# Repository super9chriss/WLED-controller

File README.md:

# WLED controller
A ESP32 C3 based microcontroller which is made to be used with WLED to use 12V or 24V ledsttrips.
I made this project since i want to add some lighting to my wall since its very dark, i wanted to learn something from this project so i made it into a devboard instead of a simpeler PCB design.
You can attach a 12 or 24V power supply to the Vin port which will directly power the ledstrip so this needs to have the same voltage rating and you can then use the ESP32 to adress the ledstrip.
<div align="center">

</div>

## Features

* **Microcontroller:** ESP32-C3-WROOM-02 with Wi-Fi and Bluetooth LE.
* **Power Input:** Supports 12V or 24V DC via dedicated screw terminals.
* **Logic Level Shifter:** Integrated SN74AHCT125DR to convert 3.3V logic to 5V for reliable LED data.
* **Connectivity:** USB-C receptacle for easy firmware flashing.
* **Led strip ports:** GPIO 1,3,4 and 5 are on the right side of the board(from bottom to top so top is 5 and bottom is 1) and can be used for ledstrips.
## How to use

1. Order the PCBA and lightstrip + powersupply.
2. Install WLED to the esp using https://install.wled.me/ if it doesnt work follow the steps on the website to install some drivers.
3. Configure WLED first connect the esp to wifi so you can remotly control the ledstrips, then add in the hardware setup which leds you are using, how many leds u use and on which pin the leds are connected(GPIO 1,3,4 and/or 5).

4. Disconnect the esp from your computer, and only then power it using the power supply also connect the ledstrip if you havent done this yet, and enjoy using the WLED controller.

## PCB and schematic
| **PCB Layout** | **Schematic** |
| :---: | :---: |
| |  |
||
||

## Wiring diagram

## BOM
|Component            |price|link                                                                                                                                                                                                                                                                          |
|---------------------|-----|------------------------------------------------------------------------------------------------------------------------------------------------------------------------------------------------------------------------------------------------------------------------------|
|ledstrip + powersuply|21.79|https://nl.aliexpress.com/item/1005007038025239.html?spm=a2g0o.cart.0.0.3f5461d7XIU4zl&mp=1&pdp_npi=6%40dis%21EUR%21EUR%2032.67%21EUR%2021.79%21%21EUR%2021.79%21%21%21%402103917f17685608530224732ebad8%2112000039180039618%21ct%21NL%21-1%21%211%210%21&gatewayAdapt=glo2nld|
|PCB                  |41.46|https://cart.jlcpcb.com/smt-order/?pcbFileNo=4c66db31f77f4dcd8bb62a3aeb8100a0                                                                                                                                                                                                 |

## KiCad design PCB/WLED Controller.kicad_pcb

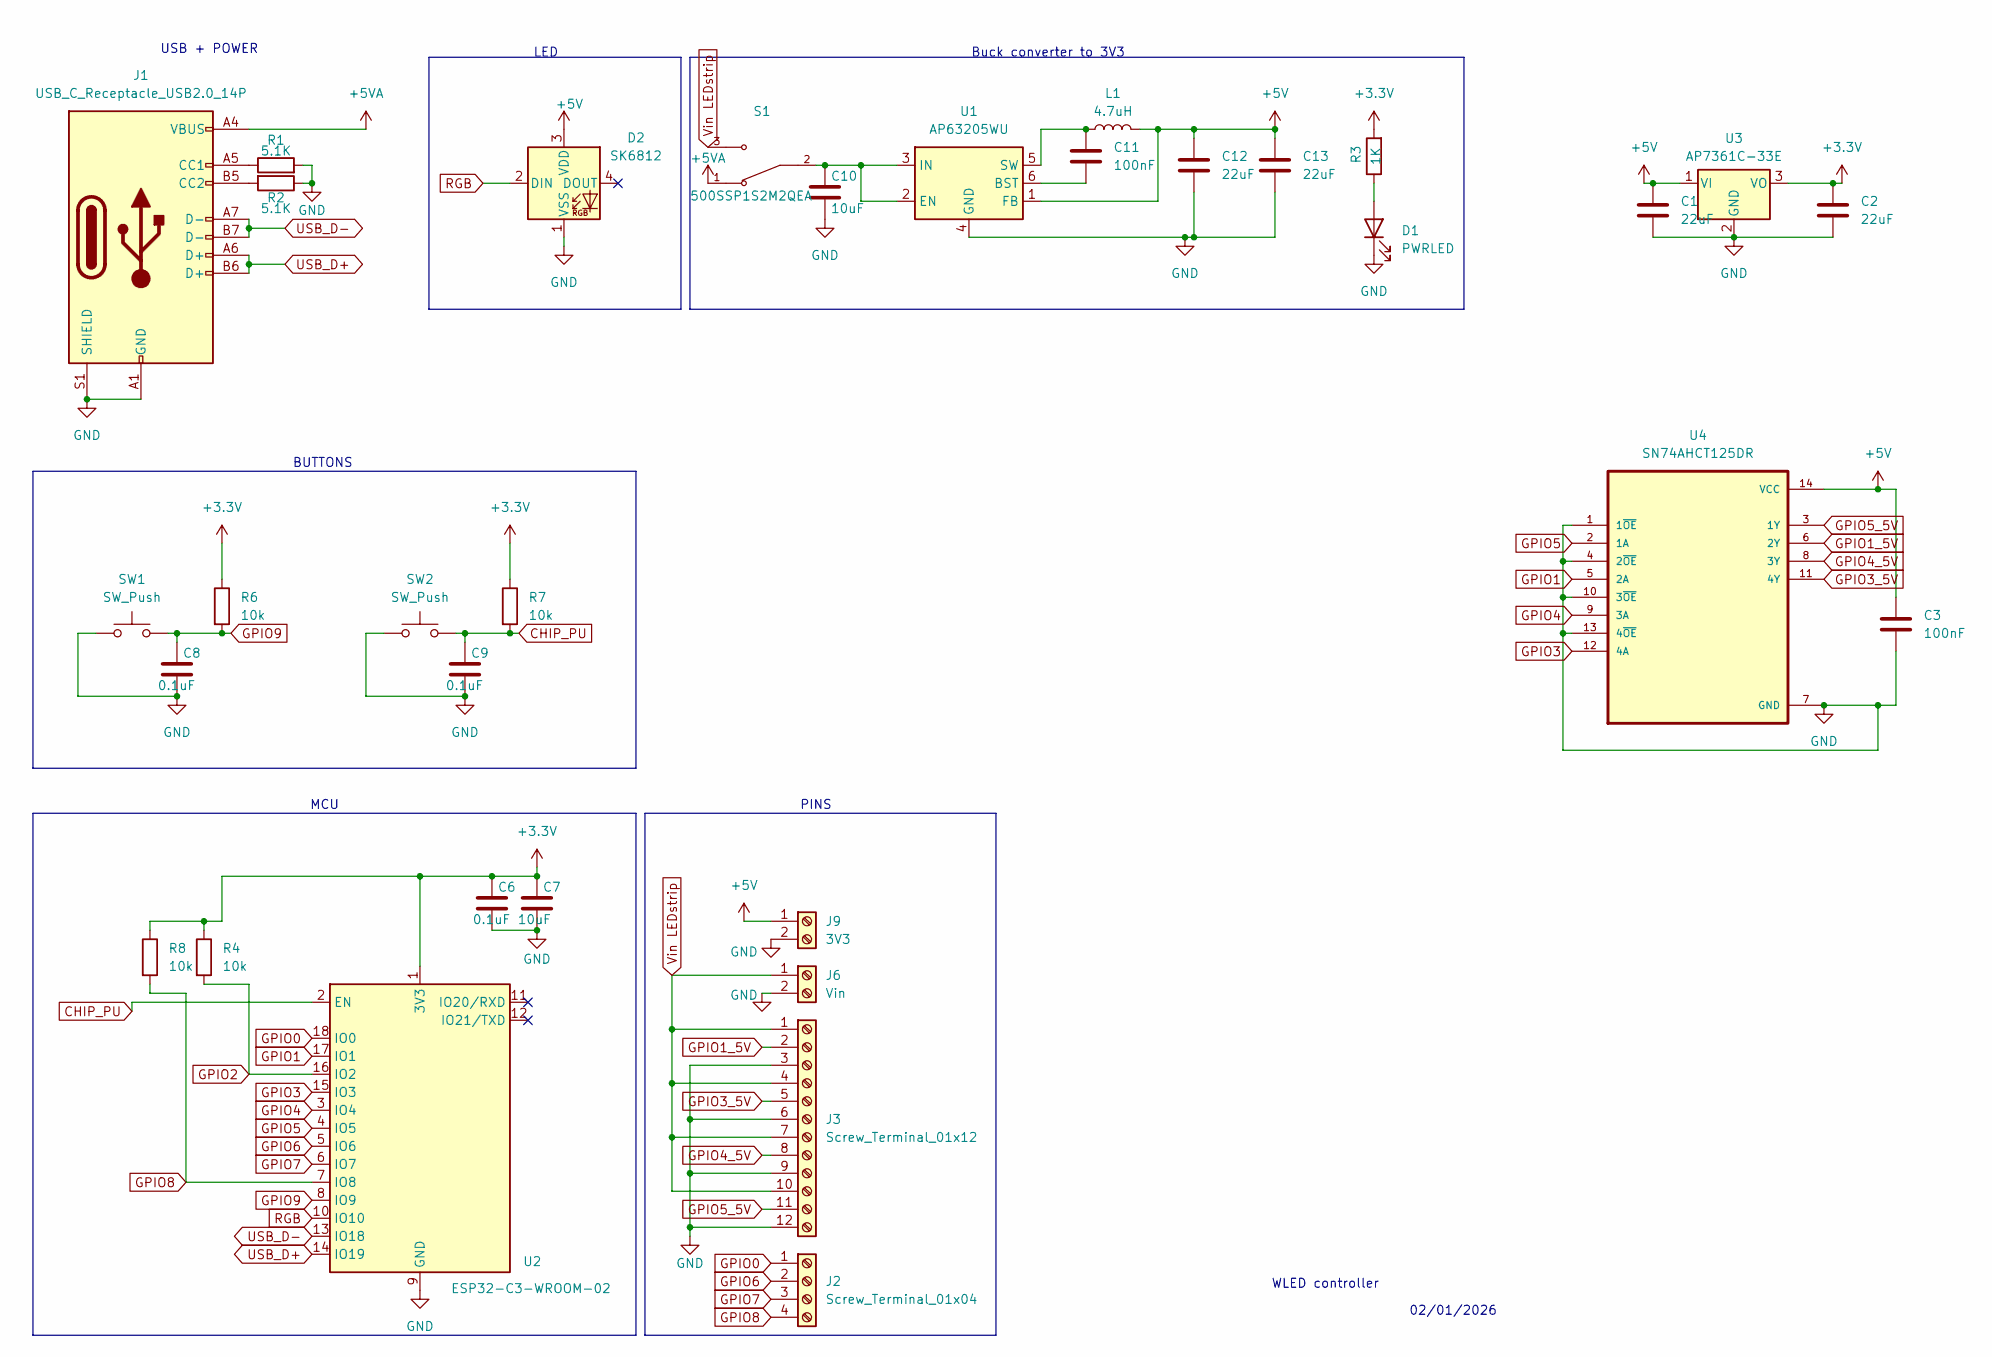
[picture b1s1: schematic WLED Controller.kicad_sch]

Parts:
C1, C2, C12, C13: 22uF; C_0603_1608Metric
C3, C11: 100nF; C_0402_1005Metric
C6, C8, C9: 0.1uF; C_0402_1005Metric
C7: 10uF; C_1206_3216Metric
C10: 10uF; C_0603_1608Metric
D1: PWRLED; LED_0603_1608Metric
D2: SK6812; LED_SK6812MINI_PLCC4_3.5x3.5mm_P1.75mm
J1: USB_C_Receptacle_USB2.0_14P; USB_C_Receptacle_HRO_TYPE-C-31-M-12
J2: Screw_Terminal_01x04; TerminalBlock_MaiXu_MX126-5.0-04P_1x04_P5.00mm
J3: Screw_Terminal_01x12; TerminalBlock_MaiXu_MX126-5.0-12P_1x12_P5.00mm
J6: Vin; TerminalBlock_MaiXu_MX126-5.0-02P_1x02_P5.00mm
J9: 3V3; TerminalBlock_MaiXu_MX126-5.0-02P_1x02_P5.00mm
L1: 4.7uH; L_Bourns-SRN8040_8x8.15mm
R1, R2: 5.1K; R_0402_1005Metric
R3: 1K; R_0402_1005Metric
R4, R6, R7, R8: 10k; R_0402_1005Metric
S1: 500SSP1S2M2QEA; SW_500SSP1S2M2QEA; PARTREV C
SW1, SW2: SW_Push; SW_PUSH_6mm
U1: AP63205WU; TSOT-23-6
U2: ESP32-C3-WROOM-02
U3: AP7361C-33E; SOT-223-3_TabPin2
U4: SN74AHCT125DR; SOIC127P600X175-14N

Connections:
+3.3V: C2.1, C6.1, C7.1, R3.2, R4.1, R6.1, R7.1, R8.1, U2.1 (3V3), U3.3 (VO)
+5V: C1.1, C3.1, C12.1, C13.1, D2.3 (VDD), J9.1, L1.2, U1.1 (FB), U3.1 (VI), U4.14 (VCC)
+5VA: J1.A4 (VBUS), J1.A9 (VBUS), J1.B4 (VBUS), J1.B9 (VBUS), S1.1
CHIP_PU: C9.1, R7.2, SW2.2, U2.2 (EN)
GND: C1.2, C2.2, C3.2, C6.2, C7.2, C8.2, C9.2, C10.2, C12.2, C13.2, D1.1 (K), D2.1 (VSS), J1.A1 (GND), J1.A12 (GND), J1.B1 (GND), J1.B12 (GND), J1.S1 (SHIELD), J3.3, J3.6, J3.9, J3.12, J6.2, J9.2, R1.2, R2.1, SW1.1, SW2.1, U1.4 (GND), U2.9 (GND), U2.19 (GND), U3.2 (GND), U4.1 (1~OE), U4.4 (2~OE), U4.7 (GND), U4.10 (3~OE), U4.13 (4~OE)
GPIO0: J2.1, U2.18 (IO0)
GPIO1: U2.17 (IO1), U4.5 (2A)
GPIO1_5V: J3.2, U4.6 (2Y)
GPIO2: R4.2, U2.16 (IO2)
GPIO3: U2.15 (IO3), U4.12 (4A)
GPIO3_5V: J3.5, U4.11 (4Y)
GPIO4: U2.3 (IO4), U4.9 (3A)
GPIO4_5V: J3.8, U4.8 (3Y)
GPIO5: U2.4 (IO5), U4.2 (1A)
GPIO5_5V: J3.11, U4.3 (1Y)
GPIO6: J2.2, U2.5 (IO6)
GPIO7: J2.3, U2.6 (IO7)
GPIO8: J2.4, R8.2, U2.7 (IO8)
GPIO9: C8.1, R6.2, SW1.2, U2.8 (IO9)
unnamed: D1.2 (A), R3.1
unnamed: J1.A5 (CC1), R1.1
unnamed: J1.B5 (CC2), R2.2
unnamed: C11.2, U1.6 (BST)
unnamed: C10.1, S1.2, U1.2 (EN), U1.3 (IN)
unnamed: C11.1, L1.1, U1.5 (SW)
RGB: D2.2 (DIN), U2.10 (IO10)
USB_D+: J1.A6 (D+), J1.B6 (D+), U2.14 (IO19)
USB_D-: J1.A7 (D-), J1.B7 (D-), U2.13 (IO18)
Vin LEDstrip: J3.1, J3.4, J3.7, J3.10, J6.1, S1.3

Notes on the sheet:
PINS
USB + POWER
02/01/2026
BUTTONS
LED
Buck converter to 3V3
MCU
WLED controller

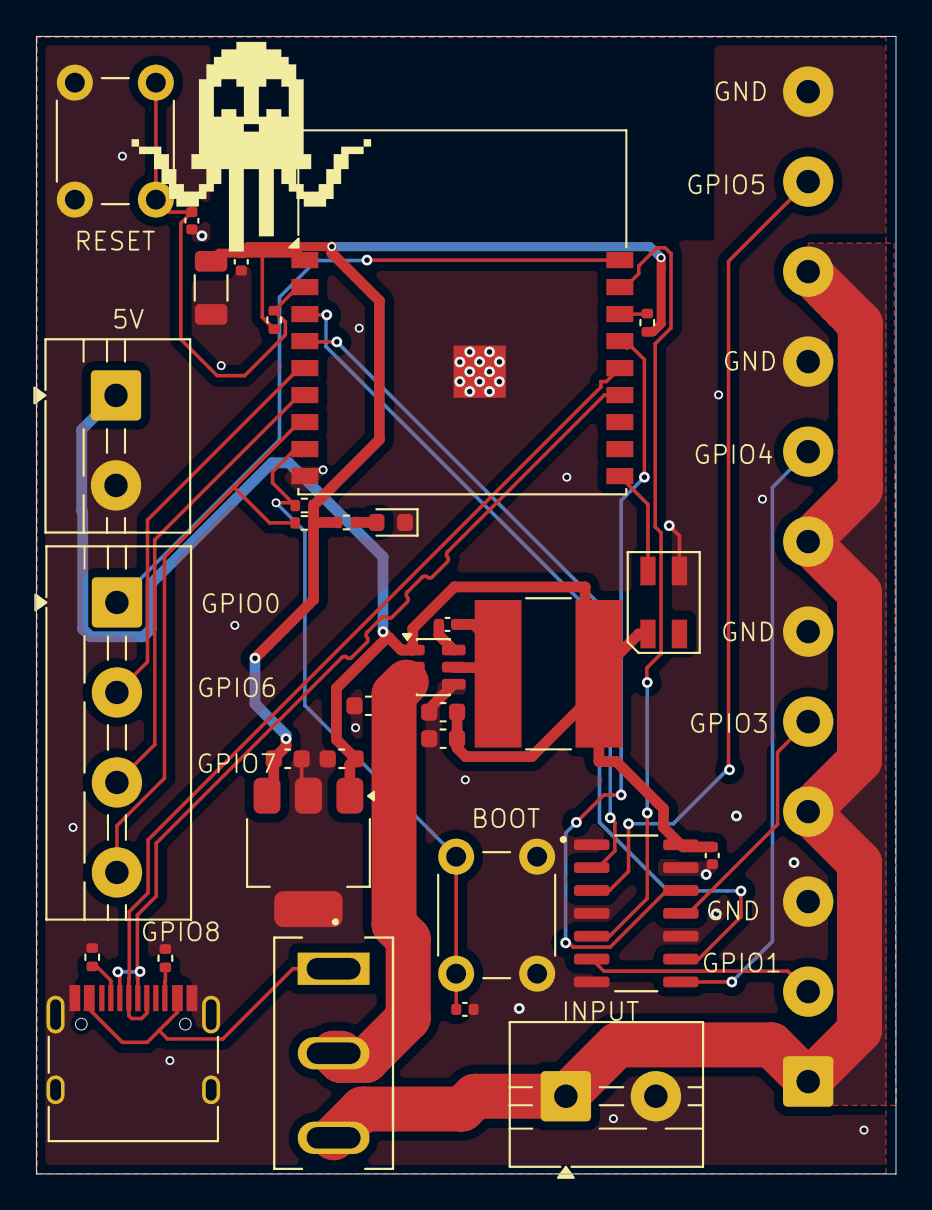
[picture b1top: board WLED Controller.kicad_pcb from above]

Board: 2 copper layers, 47.8 x 63.2 mm, 33 parts (0 on the bottom side), 29 nets.

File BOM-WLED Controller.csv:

Comment,Designator,Footprint,LCSC,Quantity
0.1uF,"C6,C8,C9",C_0402_1005Metric,C307331,3
100nF,"C11,C3",C_0402_1005Metric,C307331,2
10k,"R4,R6,R7,R8",R_0402_1005Metric,C25744,4
10uF,"C10,C7",C_0603_1608Metric,C13585,2
1K,R3,R_0402_1005Metric,C11702,1
22uF,"C1,C12,C13,C2",C_0603_1608Metric,C59461,4
3V3,J9,TerminalBlock_MaiXu_MX126-5.0-02P_1x02_P5.00mm,C1509679,1
4.7uH,L1,L_Bourns-SRN8040_8x8.15mm,C36417,1
5.1K,"R1,R2",R_0402_1005Metric,C25905,2
500SSP1S2M2QEA,S1,SW_500SSP1S2M2QEA,C92655,1
AP63205WU,U1,TSOT-23-6,C2071056,1
AP7361C-33E,U3,SOT-223-3_TabPin2,C500795,1
ESP32-C3-WROOM-02,U2,ESP32-C3-WROOM-02,C2944070,1
PWRLED,D1,LED_0603_1608Metric,C2286,1
SK6812,D2,LED_SK6812MINI_PLCC4_3.5x3.5mm_P1.75mm,C2886570,1
SN74AHCT125DR,U4,SOIC127P600X175-14N,C155176,1
SW_Push,"SW1,SW2",SW_PUSH_6mm,C111374,2
Screw_Terminal_01x04,J2,TerminalBlock_MaiXu_MX126-5.0-04P_1x04_P5.00mm,C1509680,1
Screw_Terminal_01x12,J3,TerminalBlock_MaiXu_MX126-5.0-12P_1x12_P5.00mm,C1509686,1
USB_C_Receptacle_USB2.0_14P,J1,USB_C_Receptacle_HRO_TYPE-C-31-M-12,C165948,1
Vin,J6,TerminalBlock_MaiXu_MX126-5.0-02P_1x02_P5.00mm,C1509679,1

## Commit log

2026-01-05 added files
